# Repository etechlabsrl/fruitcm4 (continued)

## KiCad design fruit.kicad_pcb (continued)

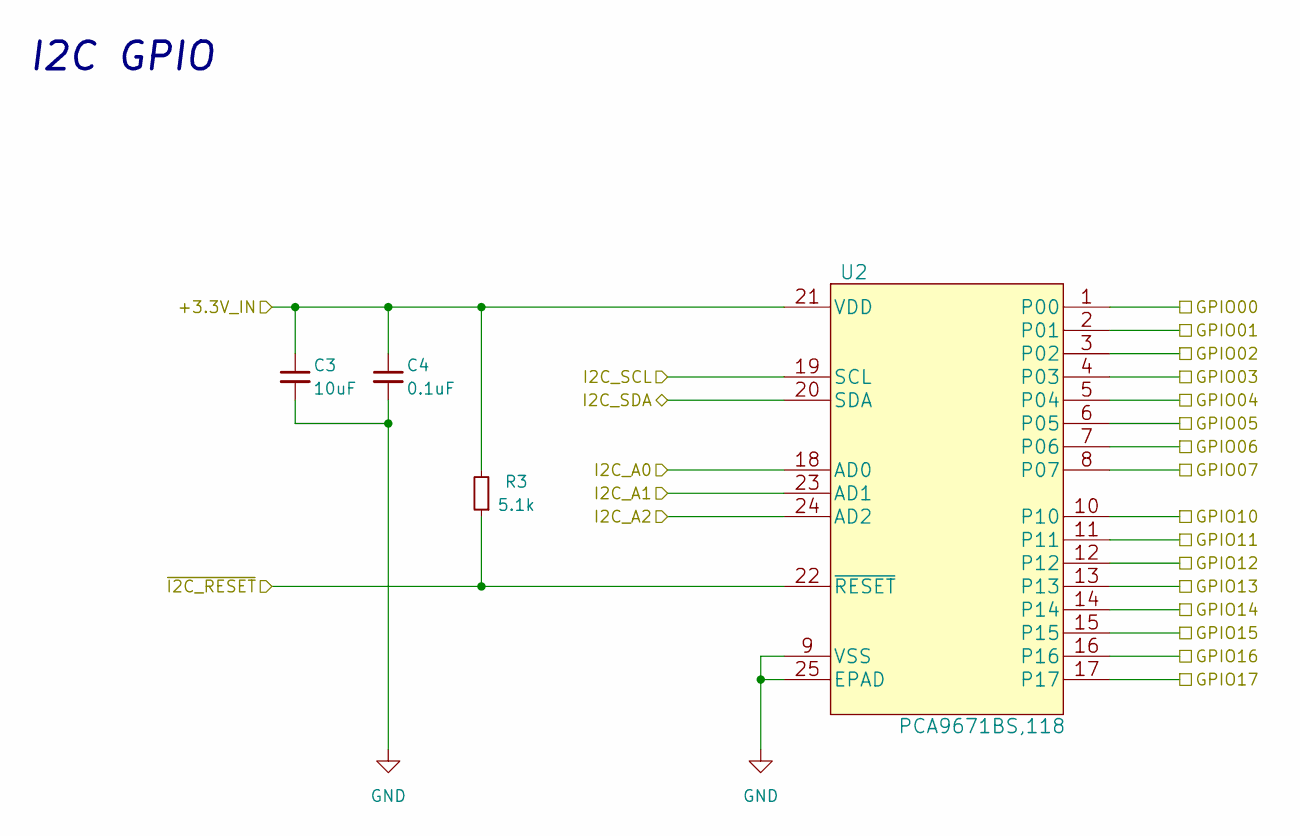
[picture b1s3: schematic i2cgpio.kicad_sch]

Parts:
C3: 10uF; C_0402_1005Metric
C4: 0.1uF; C_0402_1005Metric
R3: 5.1k; R_0402_1005Metric
U2: PCA9671BS,118; SOT616-1_HVQFN-24_4x4mm_P0.5mm_EP2.1x2.1mm_NXP; MPN PCA9671BS,118

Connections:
+12V: C3.1, C4.1, R3.2, U2.21 (VDD); also elsewhere on the board
/CM4/CM4_ALERT_+3.3V: U2.4 (P03); also elsewhere on the board
/CM4/CM4_ALERT_+5V: U2.5 (P04); also elsewhere on the board
/CM4/CM4_EN_+3.3V: U2.10; also elsewhere on the board
/CM4/CM4_EN_+5V: U2.11; also elsewhere on the board
/CM4/CM4_TALERT: U2.6 (P05); also elsewhere on the board
/CM4/I2C GPIO1/GPIO17: U2.17
/CM4/I2C GPIO1/I2C_A0: U2.18 (AD0); also elsewhere on the board
/CM4/I2C GPIO1/I2C_A1: U2.23 (AD1); also elsewhere on the board
/CM4/I2C GPIO1/I2C_A2: U2.24 (AD2); also elsewhere on the board
/CM4/I2C_GLOBAL_EN: U2.13; also elsewhere on the board
/CM4/I2C_PING_1: U2.8 (P07); also elsewhere on the board
/CM4/I2C_RUN_PG: U2.15; also elsewhere on the board
/CM4/I2C_SCL: U2.19 (SCL); also elsewhere on the board
/CM4/I2C_SDA: U2.20 (SDA); also elsewhere on the board
/CM4/M.2_TALERT: U2.7 (P06); also elsewhere on the board
/CM4/SOFT_HALT: U2.16; also elsewhere on the board
/CM4/SOFT_REBOOT: U2.14; also elsewhere on the board
/CM4/~I2C_RESET_1_2: R3.1, U2.22 (~RESET); also elsewhere on the board
/CM4/~I2C_RPI_BOOT: U2.12; also elsewhere on the board
/PRSNT_BOARD_X1_1: U2.1 (P00); also elsewhere on the board
/PRSNT_BOARD_X4_1: U2.3 (P02); also elsewhere on the board
/PRSNT_BOARD_X8_1: U2.2 (P01); also elsewhere on the board
GND: C3.2, C4.2, U2.9 (VSS), U2.25 (EPAD); also elsewhere on the board

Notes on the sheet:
I2C GPIO

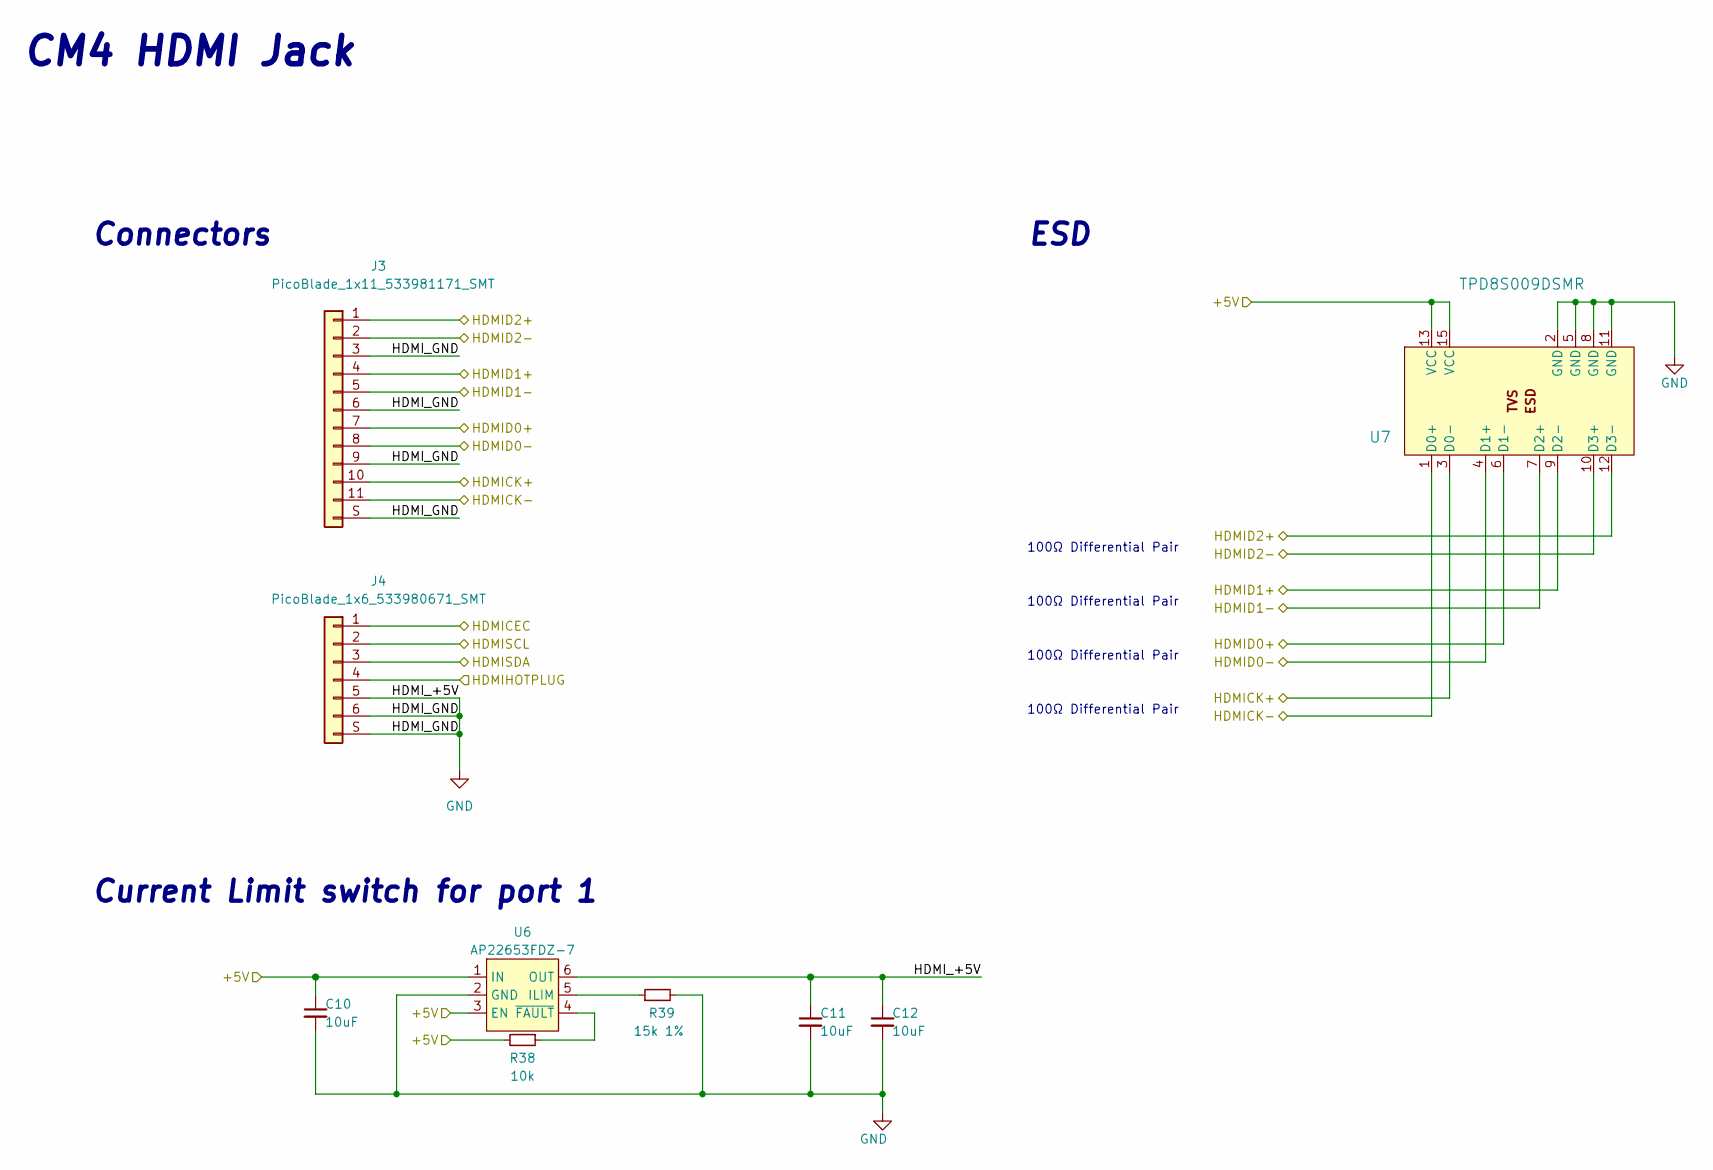
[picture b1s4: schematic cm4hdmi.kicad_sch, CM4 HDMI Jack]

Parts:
C10, C11, C12: 10uF; C_0805_2012Metric; Part Description 10uF 10% 10V Ceramic Capacitor X7R 0805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
J3: PicoBlade_1x11_533981171_SMT; MOLEX_533981171; MPN 533981171
J4: PicoBlade_1x6_533980671_SMT; MOLEX_533980671; MPN 533980771
R38: 10k; R_0402_1005Metric
R39: 15k 1%; R_0402_1005Metric; Part Description Resistor 15K M1005 1% 63mW
U6: AP22653FDZ-7; Diodes_W-DFN2020-6_A1; MPN AP22653FDZ-7
U7: TPD8S009DSMR; DSM15_X_reduced_paste_pin1; MPN TPD8S009DSMR

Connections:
/CM4/CM4_+5V: C10.1, R38.2, U6.1 (IN), U6.3 (EN), U7.13 (VCC), U7.15 (VCC); also elsewhere on the board
/CM4/HDMICEC: J4.1; also elsewhere on the board
/CM4/HDMICK+: J3.10, U7.3 (D0-); also elsewhere on the board
/CM4/HDMICK-: J3.11, U7.1 (D0+); also elsewhere on the board
/CM4/HDMID0+: J3.7, U7.6 (D1-); also elsewhere on the board
/CM4/HDMID0-: J3.8, U7.4 (D1+); also elsewhere on the board
/CM4/HDMID1+: J3.4, U7.9 (D2-); also elsewhere on the board
/CM4/HDMID1-: J3.5, U7.7 (D2+); also elsewhere on the board
/CM4/HDMID2+: J3.1, U7.12 (D3-); also elsewhere on the board
/CM4/HDMID2-: J3.2, U7.10 (D3+); also elsewhere on the board
/CM4/HDMIHP: J4.4; also elsewhere on the board
/CM4/HDMISCL: J4.2; also elsewhere on the board
/CM4/HDMISDA: J4.3; also elsewhere on the board
GND: C10.2, C11.1, C11.2, C12.1, C12.2, J3.3, J3.6, J3.9, J3.S (SHIELD), J4.5, J4.6, J4.S (SHIELD), R39.2, U6.2 (GND), U6.6 (OUT), U7.2 (GND), U7.5 (GND), U7.8 (GND), U7.11 (GND); also elsewhere on the board
unnamed: R38.1, U6.4 (~FAULT)
unnamed: R39.1, U6.5 (ILIM)

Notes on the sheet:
ESD
CM4 HDMI Jack
Connectors
100Ω Differential Pair
Current Limit switch for port 1

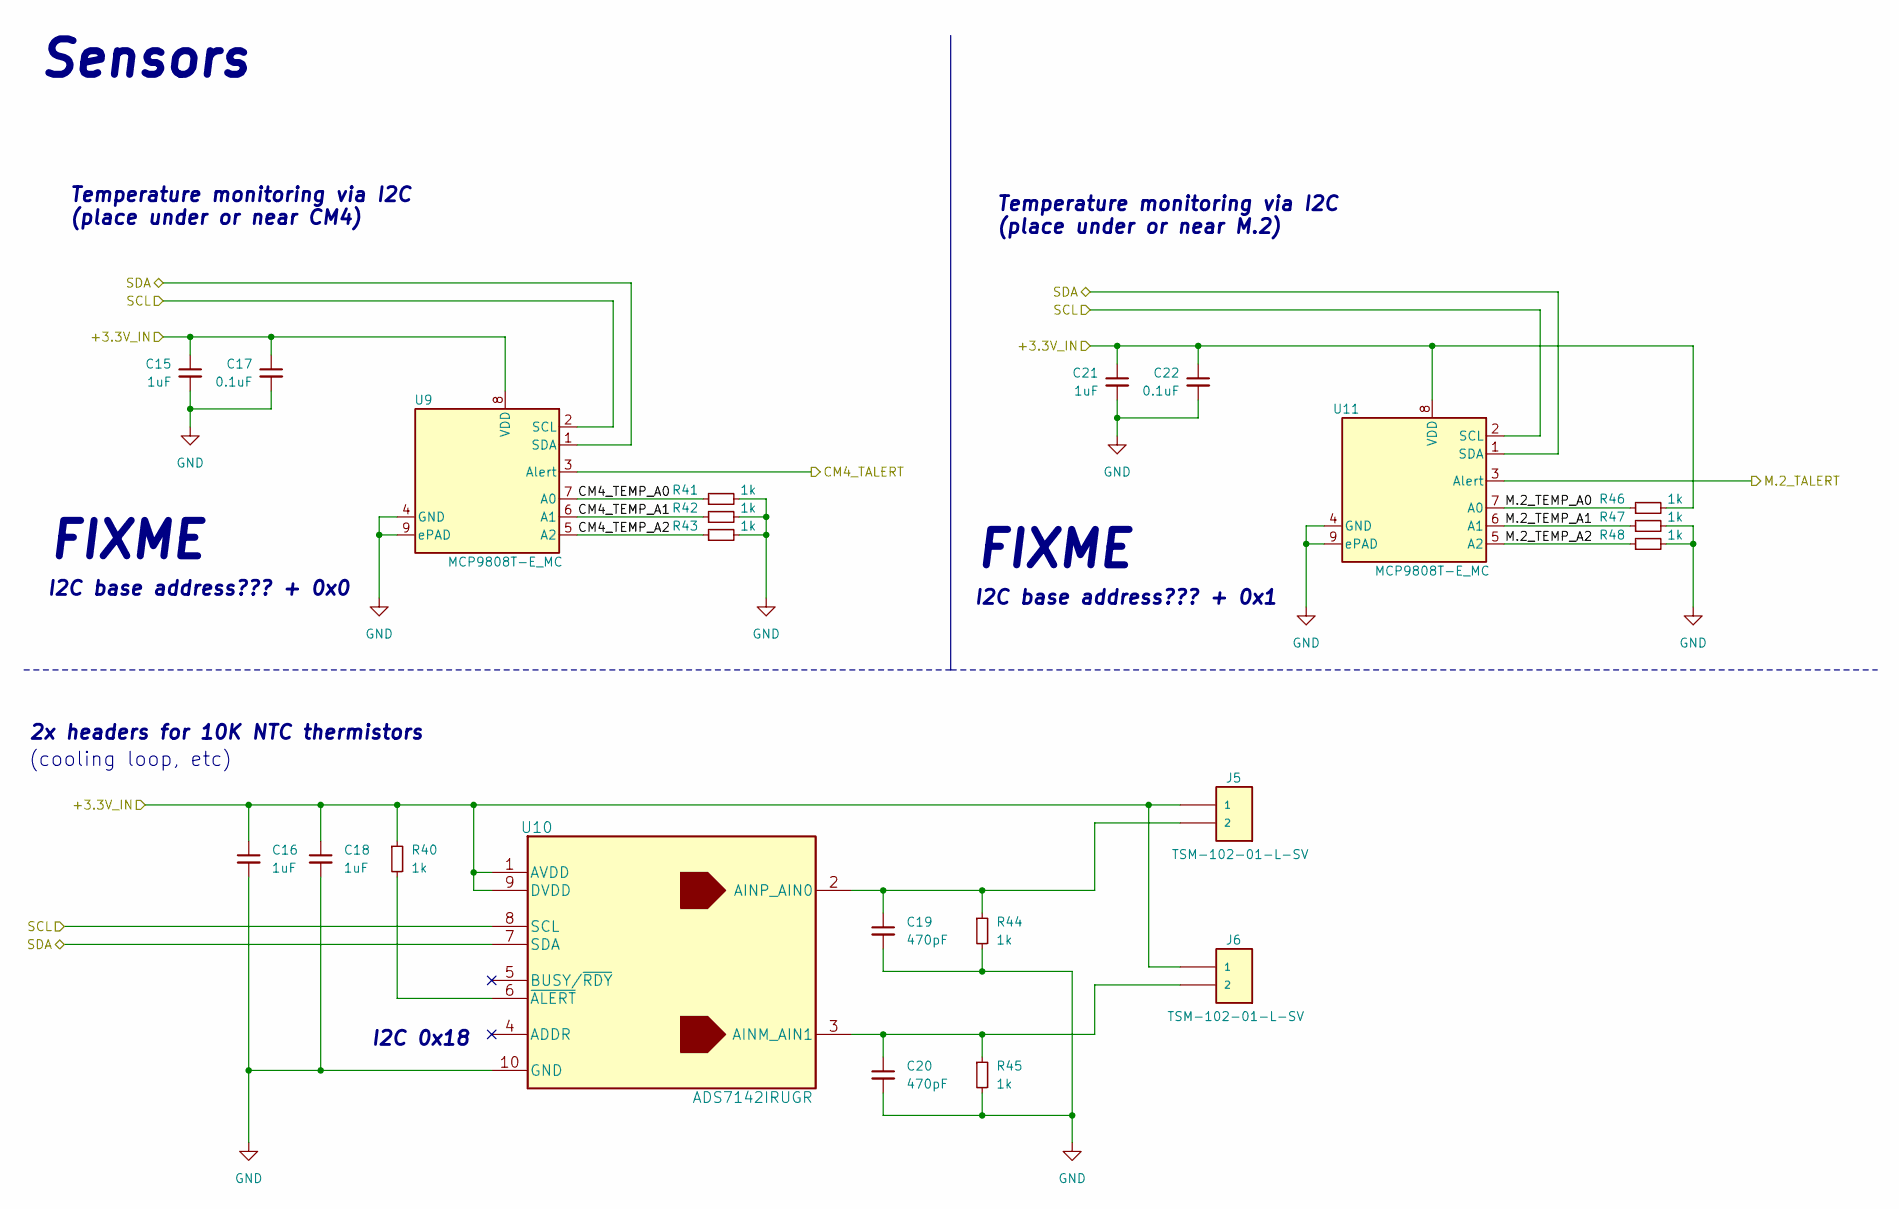
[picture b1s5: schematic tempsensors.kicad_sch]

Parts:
C15, C16, C18, C21: 1uF; C_0402_1005Metric
C17, C22: 0.1uF; C_0402_1005Metric
C19, C20: 470pF; C_0402_1005Metric
J5, J6: TSM-102-01-L-SV; SAMTEC_TSM-102-01-L-SV; MPN TSM-102-01-L-SV
R40, R41, R42, R43, R44, R45, R46, R47, R48: 1k; R_0402_1005Metric
U9, U11: MCP9808T-E_MC; MCP9808T-E&slash_MC
U10: ADS7142IRUGR; MPN ADS7142IRUGR

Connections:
+12V: C15.1, C16.1, C17.1, C18.1, C21.1, C22.1, J5.1, J6.1, R40.1, R46.2, U9.8 (VDD), U10.1 (AVDD), U10.9 (DVDD), U11.8 (VDD); also elsewhere on the board
/CM4/CM4_TALERT: U9.3 (Alert); also elsewhere on the board
/CM4/I2C_SCL: U9.2 (SCL), U10.8 (SCL), U11.2 (SCL); also elsewhere on the board
/CM4/I2C_SDA: U9.1 (SDA), U10.7 (SDA), U11.1 (SDA); also elsewhere on the board
/CM4/M.2_TALERT: U11.3 (Alert); also elsewhere on the board
/CM4/Sensors/CM4_TEMP_A0: R41.1, U9.7 (A0)
/CM4/Sensors/CM4_TEMP_A1: R42.1, U9.6 (A1)
/CM4/Sensors/CM4_TEMP_A2: R43.1, U9.5 (A2)
/CM4/Sensors/M.2_TEMP_A0: R46.1, U11.7 (A0)
/CM4/Sensors/M.2_TEMP_A1: R47.1, U11.6 (A1)
/CM4/Sensors/M.2_TEMP_A2: R48.1, U11.5 (A2)
GND: C15.2, C16.2, C17.2, C18.2, C19.2, C20.2, C21.2, C22.2, R41.2, R42.2, R43.2, R44.2, R45.2, R47.2, R48.2, U9.4 (GND), U9.9 (ePAD), U10.10 (GND), U11.4 (GND), U11.9 (ePAD); also elsewhere on the board
unnamed: C19.1, J5.2, R44.1, U10.2 (AINP_AIN0)
unnamed: C20.1, J6.2, R45.1, U10.3 (AINM_AIN1)
unnamed: R40.2, U10.6 (~ALERT)

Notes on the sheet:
Temperature monitoring via I2C (place under or near M.2)
I2C base address??? + 0x0
FIXME
I2C base address??? + 0x1
Sensors
I2C 0x18
(cooling loop, etc)
2x headers for 10K NTC thermistors
Temperature monitoring via I2C (place under or near CM4)

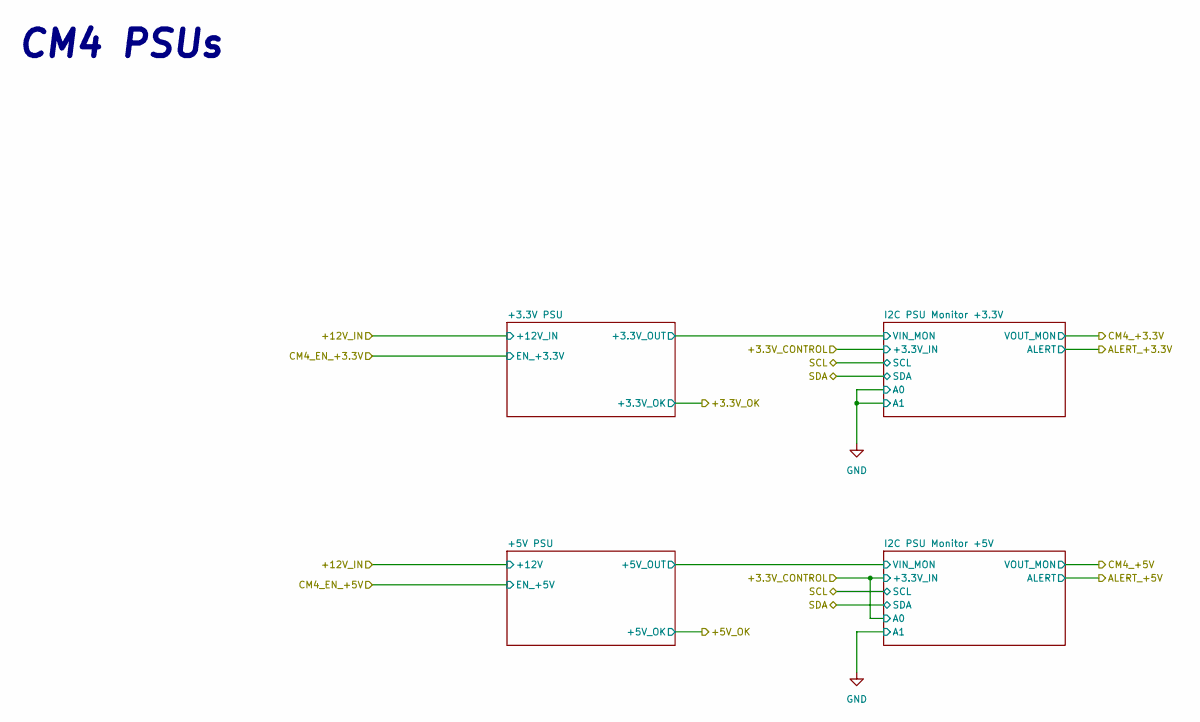
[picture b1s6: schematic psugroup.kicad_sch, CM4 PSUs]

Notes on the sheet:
CM4 PSUs

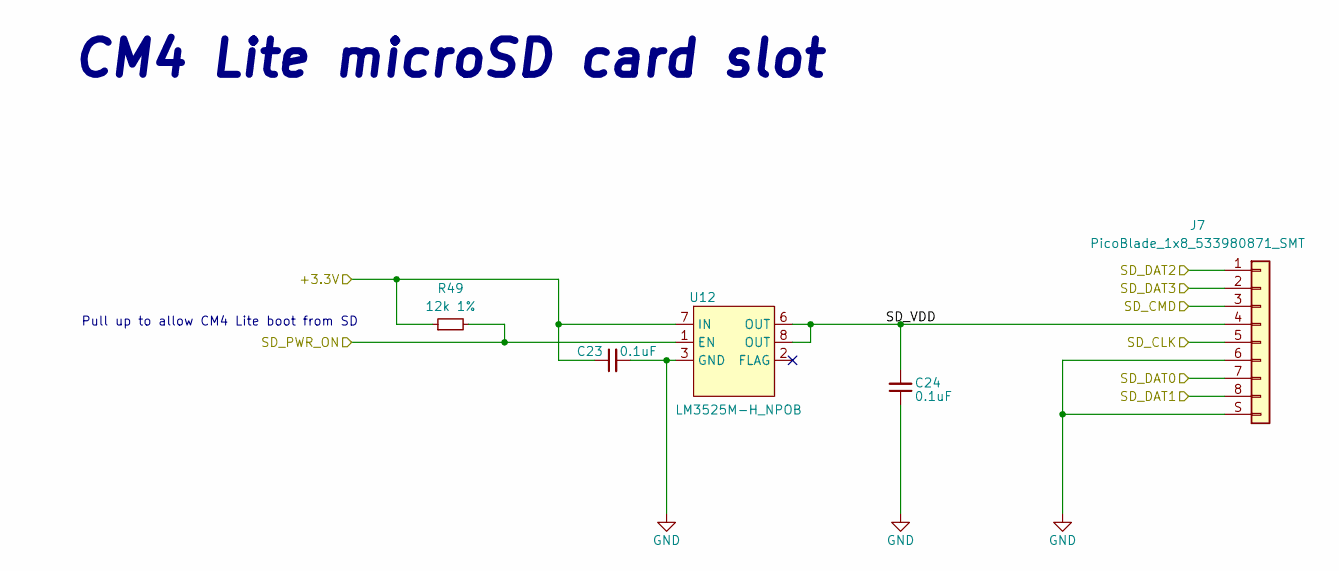
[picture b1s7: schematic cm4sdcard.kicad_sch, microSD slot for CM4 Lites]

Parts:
C23, C24: 0.1uF; C_0805_2012Metric; Part Description 10uF 10% 10V Ceramic Capacitor X7R 0805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
J7: PicoBlade_1x8_533980871_SMT; MOLEX_533980871; MPN 533980871
R49: 12k 1%; R_0402_1005Metric
U12: LM3525M-H_NPOB; SOIC-8_3.9x4.9mm_P1.27mm; MPN LM3525M-H/NPOB

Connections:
/CM4/CM4_+3.3V: C23.1, R49.1, U12.7 (IN); also elsewhere on the board
/CM4/SD_CLK: J7.5; also elsewhere on the board
/CM4/SD_CMD: J7.3; also elsewhere on the board
/CM4/SD_DAT0: J7.7; also elsewhere on the board
/CM4/SD_DAT1: J7.8; also elsewhere on the board
/CM4/SD_DAT2: J7.1; also elsewhere on the board
/CM4/SD_DAT3: J7.2; also elsewhere on the board
/CM4/SD_PWR_ON: R49.2, U12.1 (EN); also elsewhere on the board
/CM4/micro SD card/SD_VDD: C24.2, J7.4, U12.6 (OUT), U12.8 (OUT)
GND: C23.2, C24.1, J7.6, J7.S (SHIELD), U12.3 (GND); also elsewhere on the board

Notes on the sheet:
CM4 Lite microSD card slot
Pull up to allow CM4 Lite boot from SD

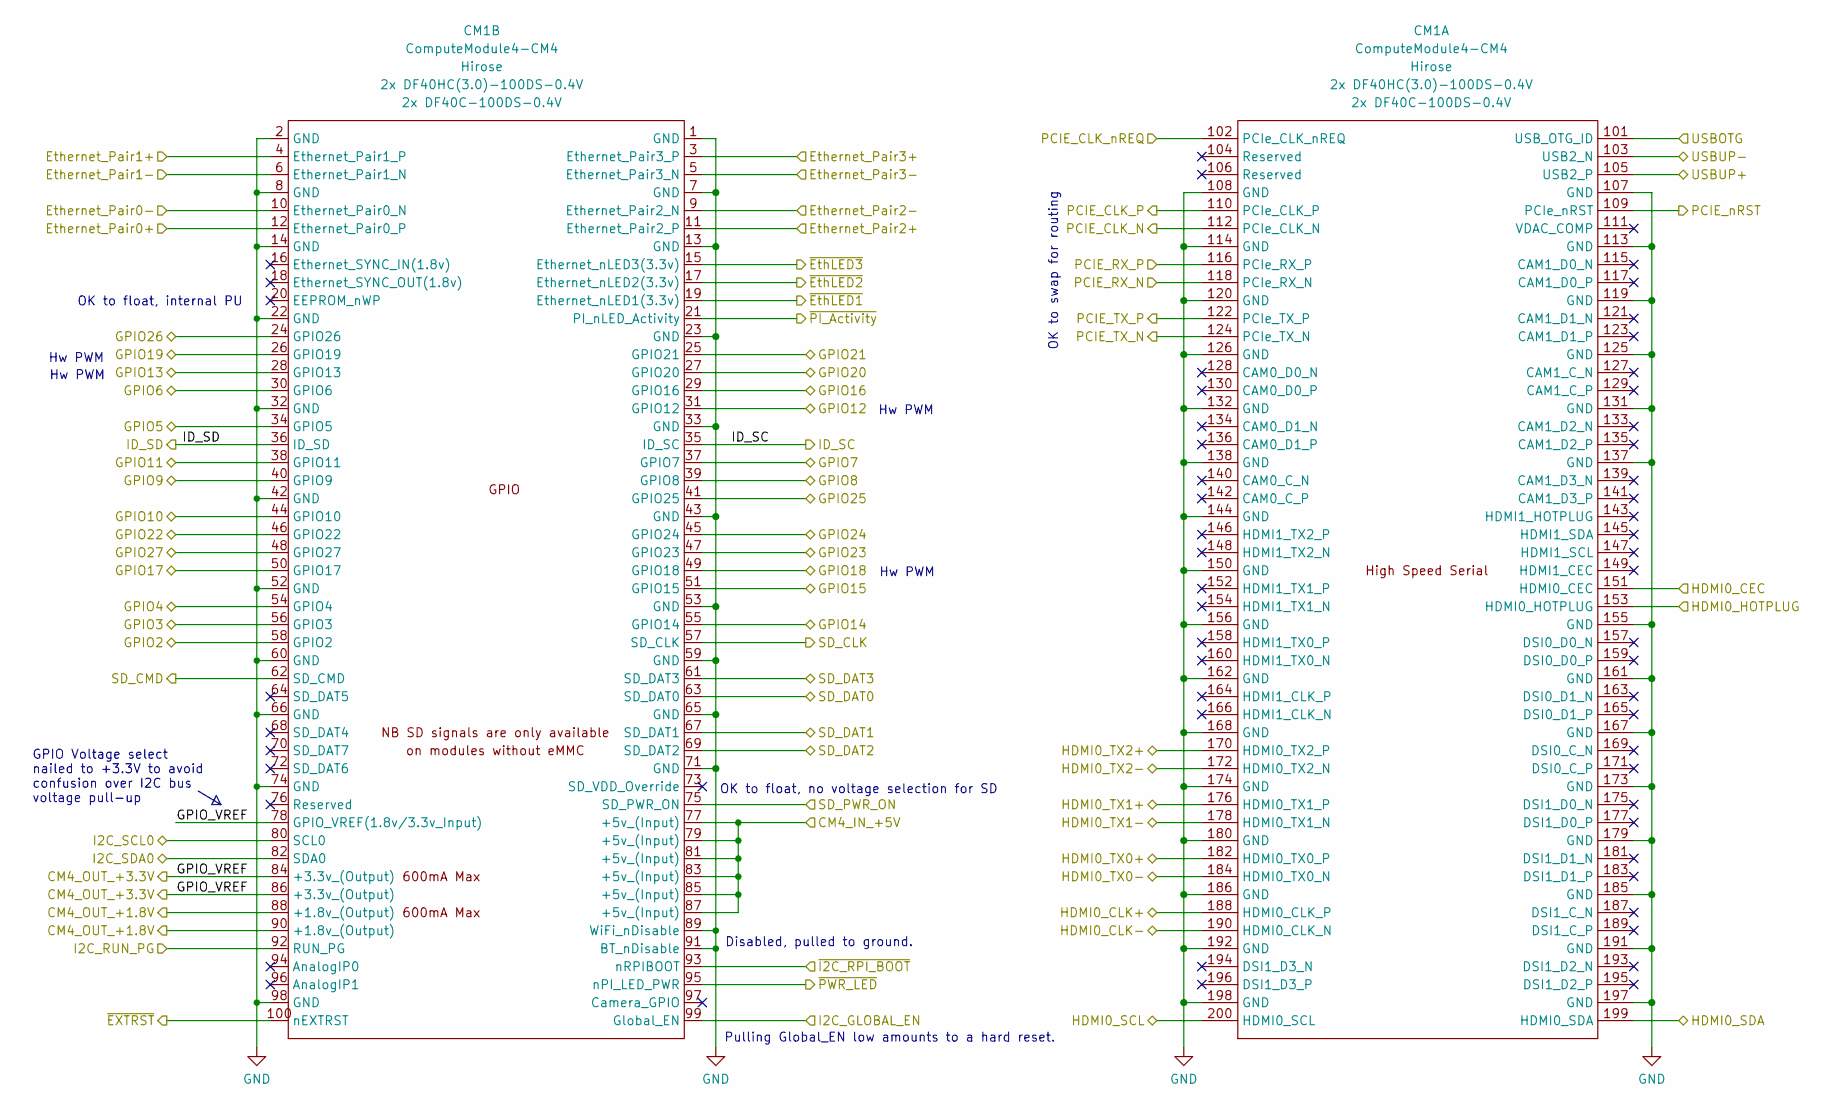
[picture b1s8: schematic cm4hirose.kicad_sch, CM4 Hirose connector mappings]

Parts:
CM1: ComputeModule4-CM4; Raspberry-Pi-4-Compute-Module_outline; MPN 2x DF40C-100DS-0.4V; Digi-Key_PN 2x H11615CT-ND

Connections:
/CM4/CM4 Hirose connectors/GPIO2: CM1.58 (GPIO2); also elsewhere on the board
/CM4/CM4 Hirose connectors/GPIO3: CM1.56 (GPIO3); also elsewhere on the board
/CM4/CM4 Hirose connectors/GPIO4: CM1.54 (GPIO4); also elsewhere on the board
/CM4/CM4 Hirose connectors/GPIO5: CM1.34 (GPIO5); also elsewhere on the board
/CM4/CM4 Hirose connectors/GPIO6: CM1.30 (GPIO6); also elsewhere on the board
/CM4/CM4 Hirose connectors/GPIO7: CM1.37 (GPIO7); also elsewhere on the board
/CM4/CM4 Hirose connectors/GPIO8: CM1.39 (GPIO8); also elsewhere on the board
/CM4/CM4 Hirose connectors/GPIO9: CM1.40 (GPIO9); also elsewhere on the board
/CM4/CM4 Hirose connectors/GPIO10: CM1.44 (GPIO10); also elsewhere on the board
/CM4/CM4 Hirose connectors/GPIO11: CM1.38 (GPIO11); also elsewhere on the board
/CM4/CM4 Hirose connectors/GPIO12: CM1.31 (GPIO12); also elsewhere on the board
/CM4/CM4 Hirose connectors/GPIO13: CM1.28 (GPIO13); also elsewhere on the board
/CM4/CM4 Hirose connectors/GPIO18: CM1.49 (GPIO18); also elsewhere on the board
/CM4/CM4 Hirose connectors/GPIO19: CM1.26 (GPIO19); also elsewhere on the board
/CM4/CM4 Hirose connectors/GPIO20: CM1.27 (GPIO20); also elsewhere on the board
/CM4/CM4 Hirose connectors/GPIO21: CM1.25 (GPIO21); also elsewhere on the board
/CM4/CM4 Hirose connectors/GPIO22: CM1.46 (GPIO22); also elsewhere on the board
/CM4/CM4 Hirose connectors/ID_SC: CM1.35 (ID_SC); also elsewhere on the board
/CM4/CM4 Hirose connectors/ID_SD: CM1.36 (ID_SD); also elsewhere on the board
/CM4/CM4 Hirose connectors/~EXTRST: CM1.100 (nEXTRST); also elsewhere on the board
/CM4/CM4_+5V: CM1.77 (+5v_(Input)), CM1.79 (+5v_(Input)), CM1.81 (+5v_(Input)), CM1.83 (+5v_(Input)), CM1.85 (+5v_(Input)), CM1.87 (+5v_(Input)); also elsewhere on the board
/CM4/CM4_I2C_SCL: CM1.80 (SCL0); also elsewhere on the board
/CM4/CM4_I2C_SDA: CM1.82 (SDA0); also elsewhere on the board
/CM4/CM4_OUT_+1.8V: CM1.88 (+1.8v_(Output)), CM1.90 (+1.8v_(Output)); also elsewhere on the board
/CM4/CM4_OUT_+3.3V: CM1.78 (GPIO_VREF(1.8v/3.3v_Input)), CM1.84 (+3.3v_(Output)), CM1.86 (+3.3v_(Output)); also elsewhere on the board
/CM4/HDMICEC: CM1.151 (HDMI0_CEC); also elsewhere on the board
/CM4/HDMICK+: CM1.188 (HDMI0_CLK_P); also elsewhere on the board
/CM4/HDMICK-: CM1.190 (HDMI0_CLK_N); also elsewhere on the board
/CM4/HDMID0+: CM1.182 (HDMI0_TX0_P); also elsewhere on the board
/CM4/HDMID0-: CM1.184 (HDMI0_TX0_N); also elsewhere on the board
/CM4/HDMID1+: CM1.176 (HDMI0_TX1_P); also elsewhere on the board
/CM4/HDMID1-: CM1.178 (HDMI0_TX1_N); also elsewhere on the board
/CM4/HDMID2+: CM1.170 (HDMI0_TX2_P); also elsewhere on the board
/CM4/HDMID2-: CM1.172 (HDMI0_TX2_N); also elsewhere on the board
/CM4/HDMIHP: CM1.153 (HDMI0_HOTPLUG); also elsewhere on the board
/CM4/HDMISCL: CM1.200 (HDMI0_SCL); also elsewhere on the board
/CM4/HDMISDA: CM1.199 (HDMI0_SDA); also elsewhere on the board
/CM4/I2C_GLOBAL_EN: CM1.99 (Global_EN); also elsewhere on the board
/CM4/I2C_RUN_PG: CM1.92 (RUN_PG); also elsewhere on the board
/CM4/PCIE_CLK+: CM1.110 (PCIe_CLK_P); also elsewhere on the board
/CM4/PCIE_CLK-: CM1.112 (PCIe_CLK_N); also elsewhere on the board
/CM4/PCIE_RX+: CM1.116 (PCIe_RX_P); also elsewhere on the board
/CM4/PCIE_RX-: CM1.118 (PCIe_RX_N); also elsewhere on the board
/CM4/PCIE_TX+: CM1.122 (PCIe_TX_P); also elsewhere on the board
/CM4/PCIE_TX-: CM1.124 (PCIe_TX_N); also elsewhere on the board
/CM4/SD_CLK: CM1.57 (SD_CLK); also elsewhere on the board
/CM4/SD_CMD: CM1.62 (SD_CMD); also elsewhere on the board
/CM4/SD_DAT0: CM1.63 (SD_DAT0); also elsewhere on the board
/CM4/SD_DAT1: CM1.67 (SD_DAT1); also elsewhere on the board
/CM4/SD_DAT2: CM1.69 (SD_DAT2); also elsewhere on the board
/CM4/SD_DAT3: CM1.61 (SD_DAT3); also elsewhere on the board
/CM4/SD_PWR_ON: CM1.75 (SD_PWR_ON); also elsewhere on the board
/CM4/SOFT_HALT: CM1.24 (GPIO26); also elsewhere on the board
/CM4/SOFT_REBOOT: CM1.48 (GPIO27); also elsewhere on the board
/CM4/USB+: CM1.105 (USB2_P); also elsewhere on the board
/CM4/USB-: CM1.103 (USB2_N); also elsewhere on the board
/CM4/USBOTG: CM1.101 (USB_OTG_ID); also elsewhere on the board
/CM4/~EthLED1: CM1.19 (Ethernet_nLED1(3.3v)); also elsewhere on the board
/CM4/~EthLED2: CM1.17 (Ethernet_nLED2(3.3v)); also elsewhere on the board
/CM4/~EthLED3: CM1.15 (Ethernet_nLED3(3.3v)); also elsewhere on the board
/CM4/~I2C_RPI_BOOT: CM1.93 (nRPIBOOT); also elsewhere on the board
/CM4/~INT_CM4: CM1.47 (GPIO23); also elsewhere on the board
/CM4/~PANIC_CM4: CM1.45 (GPIO24); also elsewhere on the board
/CM4/~PCIE_CLK_REQ: CM1.102 (PCIe_CLK_nREQ); also elsewhere on the board
/CM4/~PCIE_RST: CM1.109 (PCIe_nRST); also elsewhere on the board
/CM4/~PI_Activity: CM1.21 (PI_nLED_Activity); also elsewhere on the board
/CM4/~PWR_LED: CM1.95 (nPI_LED_PWR); also elsewhere on the board
/EthA+: CM1.12 (Ethernet_Pair0_P); also elsewhere on the board
/EthA-: CM1.10 (Ethernet_Pair0_N); also elsewhere on the board
/EthB+: CM1.4 (Ethernet_Pair1_P); also elsewhere on the board
/EthB-: CM1.6 (Ethernet_Pair1_N); also elsewhere on the board
/EthC+: CM1.11 (Ethernet_Pair2_P); also elsewhere on the board
/EthC-: CM1.9 (Ethernet_Pair2_N); also elsewhere on the board
/EthD+: CM1.3 (Ethernet_Pair3_P); also elsewhere on the board
/EthD-: CM1.5 (Ethernet_Pair3_N); also elsewhere on the board
/UART_CTS1: CM1.29 (GPIO16); also elsewhere on the board
/UART_RTS1: CM1.50 (GPIO17); also elsewhere on the board
/UART_RXD1: CM1.51 (GPIO15); also elsewhere on the board
/UART_TXD1: CM1.55 (GPIO14); also elsewhere on the board
/~I2C_RESET: CM1.41 (GPIO25); also elsewhere on the board
GND: CM1.1 (GND), CM1.2 (GND), CM1.7 (GND), CM1.8 (GND), CM1.13 (GND), CM1.14 (GND), CM1.22 (GND), CM1.23 (GND), CM1.32 (GND), CM1.33 (GND), CM1.42 (GND), CM1.43 (GND), CM1.52 (GND), CM1.53 (GND), CM1.59 (GND), CM1.60 (GND), CM1.65 (GND), CM1.66 (GND), CM1.71 (GND), CM1.74 (GND), CM1.89 (WiFi_nDisable), CM1.91 (BT_nDisable), CM1.98 (GND), CM1.107 (GND), CM1.108 (GND), CM1.113 (GND), CM1.114 (GND), CM1.119 (GND), CM1.120 (GND), CM1.125 (GND), CM1.126 (GND), CM1.131 (GND), CM1.132 (GND), CM1.137 (GND), CM1.138 (GND), CM1.144 (GND), CM1.150 (GND), CM1.155 (GND), CM1.156 (GND), CM1.161 (GND), CM1.162 (GND), CM1.167 (GND), CM1.168 (GND), CM1.173 (GND), CM1.174 (GND), CM1.179 (GND), CM1.180 (GND), CM1.185 (GND), CM1.186 (GND), CM1.191 (GND), CM1.192 (GND), CM1.197 (GND), CM1.198 (GND); also elsewhere on the board

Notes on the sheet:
OK to swap for routing
Hw PWM
OK to float, no voltage selection for SD
Disabled, pulled to ground.
Pulling Global_EN low amounts to a hard reset.
OK to float, internal PU
GPIO Voltage select nailed to +3.3V to avoid confusion over I2C bus voltage pull-up

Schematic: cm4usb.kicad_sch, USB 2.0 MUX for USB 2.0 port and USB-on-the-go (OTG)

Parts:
C25: 1uF; C_0402_1005Metric
C26: 0.1uF; C_0402_1005Metric
C27, C29, C30, C31, C32: 10uF; C_0805_2012Metric; Part Description 10uF 10% 10V Ceramic Capacitor X7R 0805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
C28: 100uF; C_1210_3225Metric
J8, J9: PicoBlade_1x6_533980671_SMT; MOLEX_533980671; MPN 533980771
R50, R54: 5.1k; R_0402_1005Metric
R51, R52: 2.2K 1%; R_0402_1005Metric; Part Description Resistor 12K M1005 1% 63mW
R53: 330R; R_0402_1005Metric; Part Description Resistor 1K M1005 1% 63mW
R55: 10k; R_0402_1005Metric
R56: 15k 1%; R_0402_1005Metric; Part Description Resistor 15K M1005 1% 63mW
U13: USB3740B-AI2; Microchip_UQFN-10_1.3x1.8mm_P0.4mm_pin1; MPN USB3740B-AI2
U14: AP22653FDZ-7; Diodes_W-DFN2020-6_A1; MPN AP22653FDZ-7

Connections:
/CM4/CM4_+3.3V: C25.1, C26.1, U13.5 (VDD); also elsewhere on the board
/CM4/CM4_+5V: C27.1, R55.2, U14.1 (IN), U14.3 (EN); also elsewhere on the board
/CM4/LED_USB_OTG_CONN: R53.1; also elsewhere on the board
/CM4/USB 2.0 MUX/HD1+: J8.3, U13.2 (DP_1)
/CM4/USB 2.0 MUX/HD1-: J8.4, U13.1 (DM_1)
/CM4/USB 2.0 MUX/HD_OTG+: J9.3, U13.6 (DP_2)
/CM4/USB 2.0 MUX/HD_OTG-: J9.4, U13.7 (DM_2)
/CM4/USB 2.0 MUX/USB1_CC1: J8.6, R50.1
/CM4/USB 2.0 MUX/USB2_CC1: J9.6, R54.1
/CM4/USB 2.0 MUX/VBUS1: C28.1, C29.1, C30.1, C31.1, C32.1, J8.1, U14.6 (OUT)
/CM4/USB 2.0 MUX/VBUS_OTG: J9.1, R51.1, R53.2
/CM4/USB+: U13.10 (DP); also elsewhere on the board
/CM4/USB-: U13.9 (DM); also elsewhere on the board
/CM4/USBOTG: R51.2, R52.1, U13.4 (S); also elsewhere on the board
GND: C25.2, C26.2, C27.2, C28.2, C29.2, C30.2, C31.2, C32.2, J8.2, J8.5, J8.S (SHIELD), J9.2, J9.5, J9.S (SHIELD), R50.2, R52.2, R54.2, R56.2, U13.3 (~OE), U13.8 (GND), U14.2 (GND); also elsewhere on the board
unnamed: R55.1, U14.4 (~FAULT)
unnamed: R56.1, U14.5 (ILIM)

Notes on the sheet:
- USB-C A5 (CC) 56K 5% resistor to VBUS - USB B6, B7 not present - A6/A7 carry DP - All VBUS pins connected (A4, B4, A9, B9) - All GND pins connected (A1, B1, A12, B12)
USB 2.0 over USB-C routing:
Always low (high disables)
Source:
Current Limit switch for port 1
USB 2.0 MUX for USB 2.0 port and USB-on-the-go (OTG)
#OTG
USB 2.0 MUX for OTG (w/ ESD)
If a cable is plugged into the UTG USB-C port, USB-C port is bypassed and CM4 acts as a USB device (VBUS_UTG high) Source: Truth table 4-1 in USB3840 datasheet ESD protection provided on all DM/DP pins.
Figure 3-23 and Table 3-13 in USB 3.1 specification
USB-C CM4-as-device (OTG) with USB 2.0 signals
S = low
USB-C connector with USB 2.0 signals
S = high

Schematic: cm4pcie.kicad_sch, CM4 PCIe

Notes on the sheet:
PCIe
PCIe x1 draws maximum of +3.3V @ 3A, use separate power supply if needed
Intentionally left blank when PCIe switch removed.
TX and RX can have PN swaps to improve routing

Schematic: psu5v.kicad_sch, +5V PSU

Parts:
C49, C50, C51, C52, C53, C54: 10uF 35V; C_1206_3216Metric; MPN GRT31CC8YA106KE01L
C55, C56: 0.1uF; C_0402_1005Metric; MPN CGA2B1X7R1C104K050BC
C57: DNP; C_0402_1005Metric
C58: 1.2nF; C_0402_1005Metric; Part Description 1200pF 10% 10V Ceramic Capacitor X5R 04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
C59: DNP; C_0402_1005Metric; Part Description 220 pF, 50 V, 0402 [1005 Metric], ± 5%,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
C60, C61, C62, C63: 10uF; C_0805_2012Metric; MPN LMK212B7106KG-TD
C64: 100uF; CP_EIA-7343-31_Kemet-D; MPN T495D107K006ATE130
L2: SRN6045TA-3R3Y; L_Bourns_SRN6045TA; Part Description 3.3µH Semi-Shielded Wirewound Inductor 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
R62: 10R; R_0402_1005Metric; Part Description Resistor 10R M1005 1% 63mW
R63: 20k 1%; R_0402_1005Metric; MPN AC0402FR-0720KL
R64: 12k 1%; R_0402_1005Metric; MPN AC0402FR-0712KL
R65: 2.2K 1%; R_0402_1005Metric; MPN AC0402FR-072K2L
R66: 600R; R_0402_1005Metric
TP13, TP14: TestPoint; TestPoint_Pad_D1.0mm
U16: AP64501SP-13; SOIC-8-1EP_3.9x4.9mm_P1.27mm_EP2.95x4.9mm_Mask2.71x3.4mm_Th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; MPN AP64501SP-13

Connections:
+3.3V: C49.1, C50.1, C51.1, C52.1, C53.1, C54.1, U16.2 (VIN); also elsewhere on the board
/CM4/CM4 PSU/+5V PSU/+5V_OUT: C60.1, C61.1, C62.1, C63.1, C64.1, L2.2, R64.1, R66.1, TP13.1; also elsewhere on the board
/CM4/CM4_EN_+5V: U16.3 (EN); also elsewhere on the board
/CM4/LED_+5V_OK_CONN: R66.2; also elsewhere on the board
GND: C49.2, C50.2, C51.2, C52.2, C53.2, C54.2, C56.2, C58.2, C60.2, C61.2, C62.2, C63.2, C64.2, R65.2, TP14.1, U16.7 (GND), U16.9 (EP); also elsewhere on the board
unnamed: C55.1, R62.2
unnamed: C55.2, U16.1 (BST)
unnamed: C56.1, U16.4 (SS)
unnamed: C58.1, R63.2
unnamed: L2.1, R62.1, U16.8 (SW)
unnamed: R63.1, U16.6 (COMP)
unnamed: R64.2, R65.1, U16.5 (FB)

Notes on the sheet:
< PSU On LED
+5V PSU @ 3A peak
+5v @ 3A PSU ( 7.5v-28v Input )
NB: Borrowed/Inspired by Raspberry Pi Foundation's CM4IO
NB: Use GND testpoint from 3.3V PSU

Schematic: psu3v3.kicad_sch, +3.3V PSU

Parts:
C33, C34, C35, C36, C37, C38: 10uF 35V; C_1206_3216Metric; MPN GRT31CC8YA106KE01L
C39, C40: 0.1uF; C_0402_1005Metric; MPN CGA2B1X7R1C104K050BC
C41, C43: DNP; C_0402_1005Metric
C42: 1.2nF; C_0402_1005Metric; MPN GCM155R71H122KA37D
C44, C45, C46, C47: 10uF; C_0805_2012Metric; MPN LMK212B7106KG-TD
C48: 100uF; CP_EIA-7343-31_Kemet-D; MPN T495D107K006ATE130
L1: SRN6045TA-3R3Y; L_Bourns_SRN6045TA; MPN SRN6045TA-3R3Y
R57: 10R; R_0402_1005Metric; MPN AC0402FR-0710RL
R58: 12k 1%; R_0402_1005Metric; MPN AC0402FR-0712KL
R59: 47k 1%; R_0402_1005Metric; MPN RC0402FR-0747KL
R60: 15k 1%; R_0402_1005Metric; MPN AC0402FR-0715KL
R61: 260R; R_0402_1005Metric
TP11, TP12: TestPoint; TestPoint_Pad_D1.0mm
U15: AP64501SP-13; SOIC-8-1EP_3.9x4.9mm_P1.27mm_EP2.95x4.9mm_Mask2.71x3.4mm_Th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; MPN AP64501SP-13

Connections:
+3.3V: C33.1, C34.1, C35.1, C36.1, C37.1, C38.1, U15.2 (VIN); also elsewhere on the board
/CM4/CM4 PSU/+3.3V PSU/+3.3V_OUT: C44.1, C45.1, C46.1, C47.1, C48.1, L1.2, R59.1, R61.1, TP12.1; also elsewhere on the board
/CM4/CM4_EN_+3.3V: U15.3 (EN); also elsewhere on the board
/CM4/LED_+3.3V_OK_CONN: R61.2; also elsewhere on the board
GND: C33.2, C34.2, C35.2, C36.2, C37.2, C38.2, C40.2, C42.2, C44.2, C45.2, C46.2, C47.2, C48.2, R60.2, TP11.1, U15.7 (GND), U15.9 (EP); also elsewhere on the board
unnamed: C39.1, R57.2
unnamed: C39.2, U15.1 (BST)
unnamed: C40.1, U15.4 (SS)
unnamed: C42.1, R58.2
unnamed: L1.1, R57.1, U15.8 (SW)
unnamed: R58.1, U15.6 (COMP)
unnamed: R59.2, R60.1, U15.5 (FB)

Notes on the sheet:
NB: Borrowed/Inspired by Raspberry Pi Foundation's CM4IO
3.3v @ 3.3A PSU for PCIe Only ( 12v Input )
+3.3V PSU @ 3A peak
< PSU On LED

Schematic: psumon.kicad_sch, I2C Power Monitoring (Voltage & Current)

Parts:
C13: 10uF; C_0402_1005Metric
C14: 0.1uF; C_0402_1005Metric
TP10: TestPoint; TestPoint_Pad_D1.0mm
U8: INA260; TSSOP-16_4.4x5mm_P0.65mm_pin1; MPN INA260AIPW

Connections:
+12V: C13.1, C14.1, U8.10 (VS); also elsewhere on the board
/CM4/CM4 PSU/+3.3V PSU/+3.3V_OUT: U8.1 (IN+), U8.2 (IN+), U8.3 (IN+), U8.12 (VBUS); also elsewhere on the board
/CM4/CM4_+3.3V: TP10.1, U8.14 (IN-), U8.15 (IN-), U8.16 (IN-); also elsewhere on the board
/CM4/CM4_ALERT_+3.3V: U8.7 (ALERT); also elsewhere on the board
/CM4/I2C_SCL: U8.9 (SCL); also elsewhere on the board
/CM4/I2C_SDA: U8.8 (SDA); also elsewhere on the board
GND: C13.2, C14.2, U8.4 (A1), U8.5 (A0), U8.6 (GND), U8.11 (GND); also elsewhere on the board

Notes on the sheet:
Voltage & Current
I2C Power Monitoring

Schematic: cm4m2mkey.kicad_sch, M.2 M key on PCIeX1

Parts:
C65, C66, C67: 10uF; C_0402_1005Metric
C68, C69: 1uF; C_0402_1005Metric
C70, C71, C72, C73, C74: 10nF; C_0402_1005Metric
C75: 0.1uF; C_0402_1005Metric
J10: 1-2199119-6; 1-2199119-6_2280_standoff_nooutline
R67, R68, R69, R70, R71, R72, R73, R74, R75, R76, R77, R78, R79, R80: 50R; R_0402_1005Metric

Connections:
/CM4/CM4_+3.3V: C65.1, C66.1, C67.1, C68.1, C69.1, C70.1, C71.1, C72.1, C73.1, C74.1, C75.1, J10.2 (3.3V), J10.4 (3.3V), J10.12 (3.3V), J10.14 (3.3V), J10.16 (3.3V), J10.18 (3.3V), J10.70 (3.3V), J10.72 (3.3V), J10.74 (3.3V); also elsewhere on the board
/CM4/M2_1_ACTIVITY_LED: J10.10 (DAS/DSS); also elsewhere on the board
/CM4/PCIE_CLK+: J10.55 (REFCLK+), R68.1; also elsewhere on the board
/CM4/PCIE_CLK-: J10.53 (REFCLK-), R67.1; also elsewhere on the board
/CM4/PCIE_RX+: J10.43 (PER0+); also elsewhere on the board
/CM4/PCIE_RX-: J10.41 (PER0-); also elsewhere on the board
/CM4/PCIE_TX+: J10.47 (PET0-); also elsewhere on the board
/CM4/PCIE_TX-: J10.49 (PET0+); also elsewhere on the board
/CM4/~PCIE_CLK_REQ: J10.52 (~CLKREQ); also elsewhere on the board
/CM4/~PCIE_RST: J10.50 (~PERST); also elsewhere on the board
GND: C65.2, C66.2, C67.2, C68.2, C69.2, C70.2, C71.2, C72.2, C73.2, C74.2, C75.2, J10.1 (GND), J10.3 (GND), J10.9 (GND), J10.15 (GND), J10.21 (GND), J10.27 (GND), J10.33 (GND), J10.39 (GND), J10.45 (GND), J10.51 (GND), J10.57 (GND), J10.71 (GND), J10.73 (GND), J10.75 (GND), J10.S (SHIELD), R67.2, R68.2, R69.1, R70.1, R71.1, R72.1, R73.1, R74.1, R75.1, R76.1, R77.1, R78.1, R79.1, R80.1; also elsewhere on the board
unnamed 152: J10.5 (PER3-), R69.2; also elsewhere on the board
unnamed 153: J10.7 (PER+), R70.2; also elsewhere on the board
unnamed 154: J10.11 (PET3-), R71.2; also elsewhere on the board
unnamed 155: J10.13 (PET3+), R72.2; also elsewhere on the board
unnamed 156: J10.17 (PER2-), R73.2; also elsewhere on the board
unnamed 157: J10.19 (PER2+), R74.2; also elsewhere on the board
unnamed 158: J10.23 (PET2-), R75.2; also elsewhere on the board
unnamed 159: J10.25 (PET2+), R76.2; also elsewhere on the board
unnamed 160: J10.29 (PER1-), R77.2; also elsewhere on the board
unnamed 161: J10.31 (PER1+), R78.2; also elsewhere on the board
unnamed 162: J10.35 (PET1-), R79.2; also elsewhere on the board
unnamed 163: J10.37 (PET1+), R80.2; also elsewhere on the board

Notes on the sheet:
90Ω Differential Pair
H or NC = PCIe
M.2 M key on PCIeX1
TX and RX can have PN swaps to improve routing
PCIe x1 draws maximum of +3.3V @ 3A, use separate power supply if needed
(instead of SATA)
